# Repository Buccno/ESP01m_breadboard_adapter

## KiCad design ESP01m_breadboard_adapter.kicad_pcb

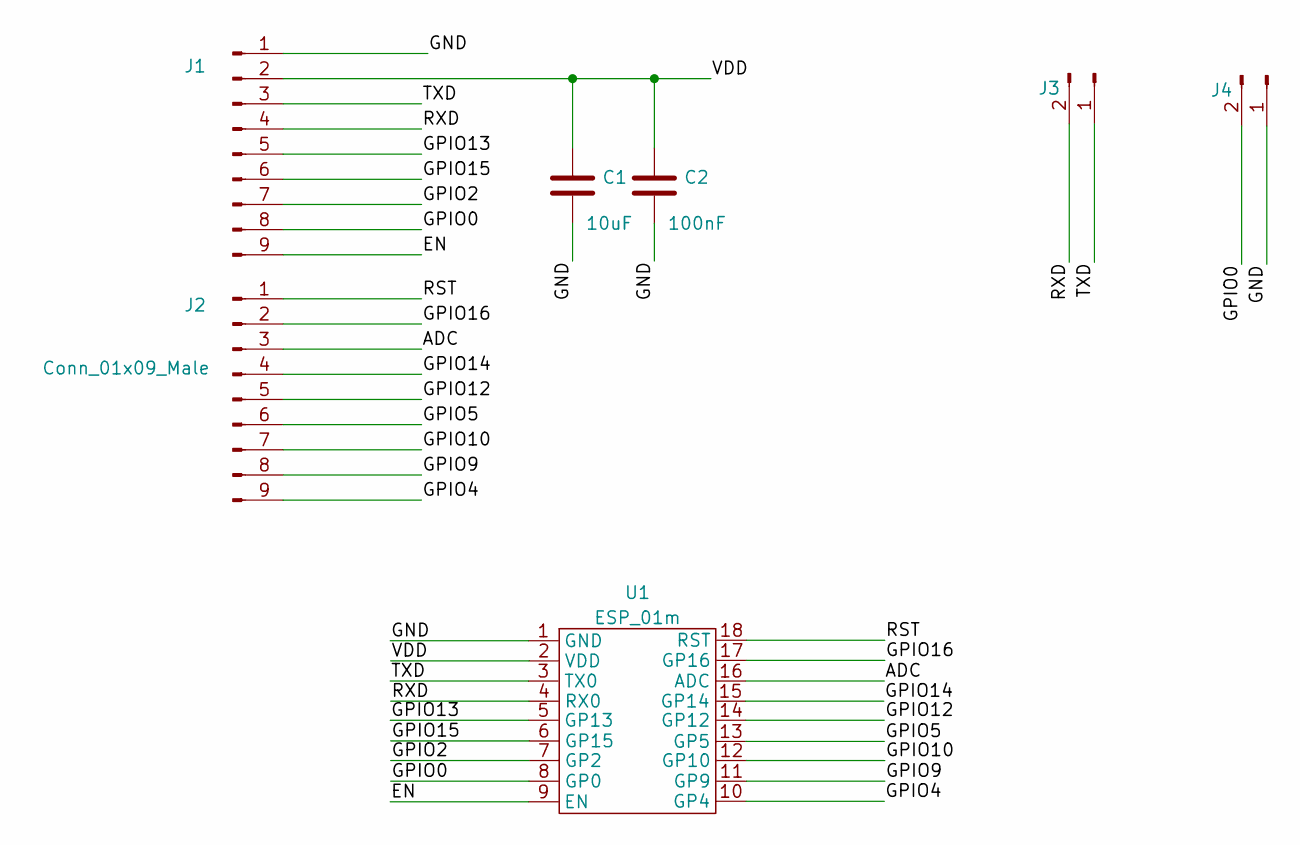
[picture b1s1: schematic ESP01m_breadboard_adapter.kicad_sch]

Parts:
C1: 10uF; CP_Radial_D8.0mm_P5.00mm
C2: 100nF; CP_Radial_D8.0mm_P5.00mm
J1, J2: Conn_01x09_Male; PinHeader_1x09_P2.54mm_Vertical
J3, J4: Conn_01x02_Male; PinHeader_1x02_P2.54mm_Vertical
U1: ESP_01m; ESP_01M

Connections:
/ADC: J2.3, U1.16 (ADC)
/EN: J1.9, U1.9 (EN)
/GND: C1.2, C2.2, J1.1, J4.1, U1.1 (GND)
/GPIO0: J1.8, J4.2, U1.8 (GP0)
/GPIO2: J1.7, U1.7 (GP2)
/GPIO4: J2.9, U1.10 (GP4)
/GPIO5: J2.6, U1.13 (GP5)
/GPIO9: J2.8, U1.11 (GP9)
/GPIO10: J2.7, U1.12 (GP10)
/GPIO12: J2.5, U1.14 (GP12)
/GPIO13: J1.5, U1.5 (GP13)
/GPIO14: J2.4, U1.15 (GP14)
/GPIO15: J1.6, U1.6 (GP15)
/GPIO16: J2.2, U1.17 (GP16)
/RST: J2.1, U1.18 (RST)
/RXD: J1.4, J3.2, U1.4 (RX0)
/TXD: J1.3, J3.1, U1.3 (TX0)
/VDD: C1.1, C2.1, J1.2, U1.2 (VDD)

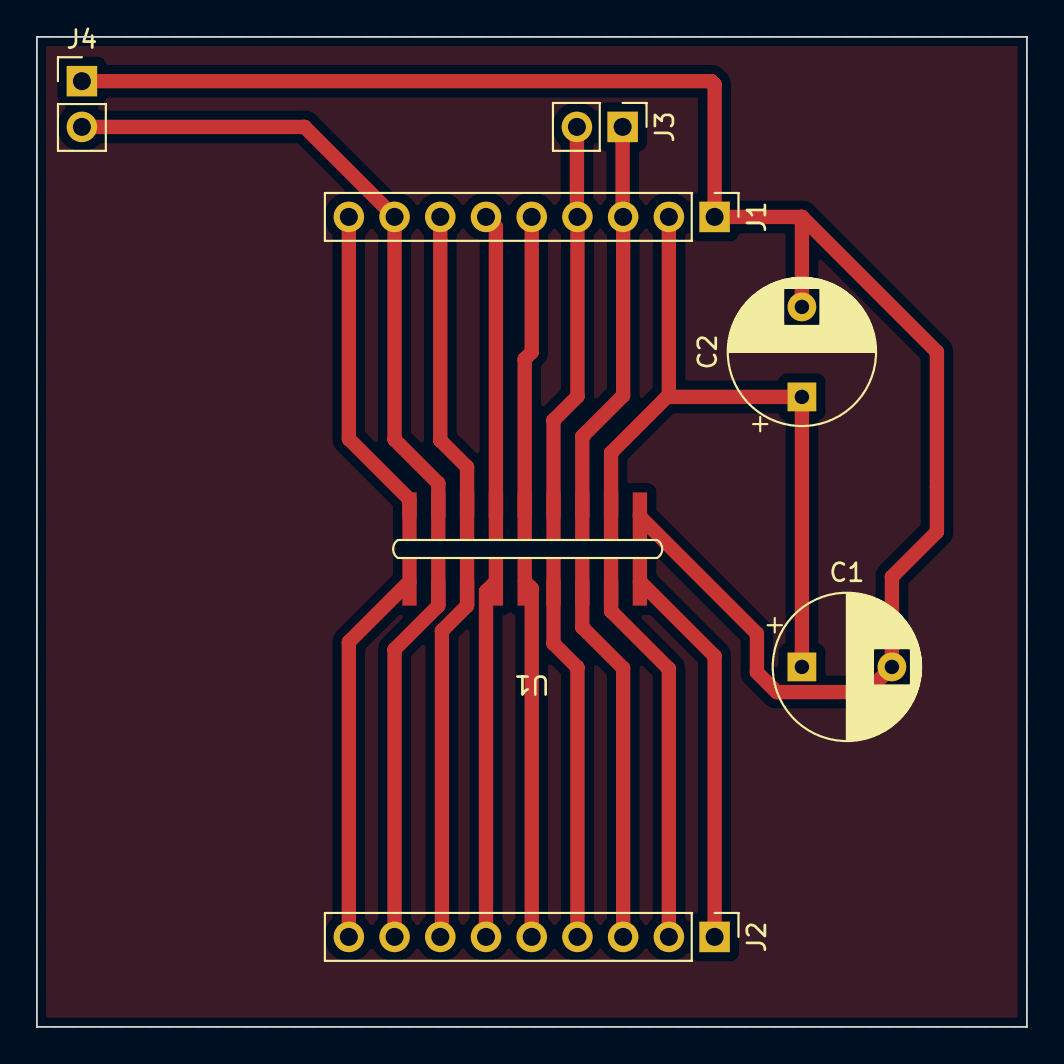
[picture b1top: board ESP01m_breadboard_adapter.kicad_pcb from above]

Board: 2 copper layers, 55.0 x 55.0 mm, 7 parts (0 on the bottom side), 18 nets.

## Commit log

2022-06-29 Added Kicad files ESP01m adapters
